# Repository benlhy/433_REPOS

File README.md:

# 433_REPOS
## Link to Homework 1
https://github.com/ndm736/ME433_2018/wiki/HW1

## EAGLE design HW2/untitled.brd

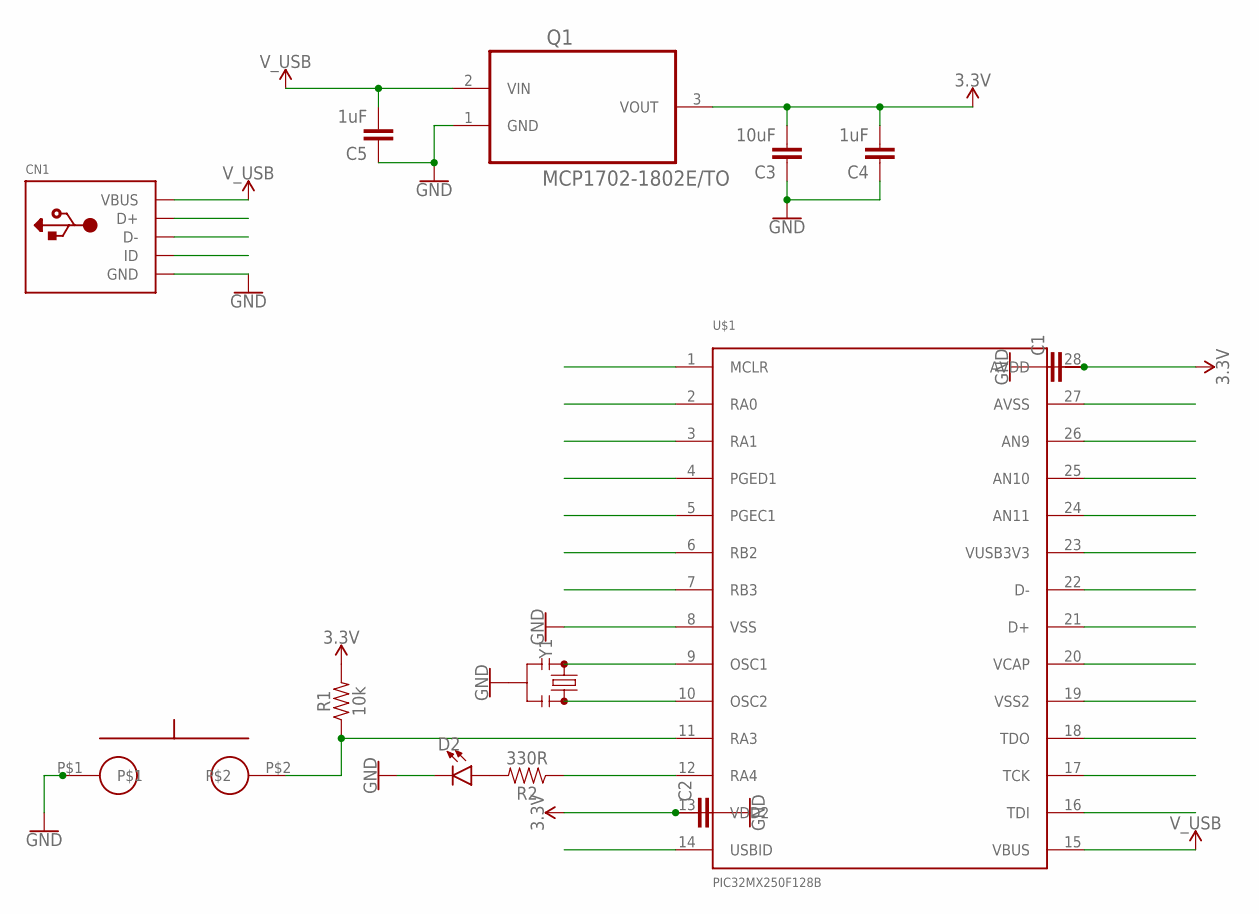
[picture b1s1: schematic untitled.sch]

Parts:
C1, C2: CAPVERT_CAP; PTH_VERT_CAP
C3: 10uF; PTH_VERT_CAP
C4, C5: 1uF; PTH_VERT_CAP
CN1: USBMINIB; USB-MINIB
D2: LED3MM; LED_3MM
Q1: MCP1702-1802E/TO; TO127P254X533-3
R1: 10k; AXIAL-0.3
R2: 330R; AXIAL-0.3
U$1: PIC32MX250F128B; DIP28
U$2: EVQ11
Y1: RESONATORPTH-7.6X3.8; RESONATOR-PTH-7.6X3.8

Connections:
3.3V: C1.P$2 (2), C2.P$1 (1), C3.P$2 (2), C4.P$2 (2), Q1.3 (VOUT), R1.P$2 (2), U$1.13 (VDD2), U$1.28 (AVDD)
D+: CN1.D+, U$1.21 (D+)
D-: CN1.D-, U$1.22 (D-)
GND: C1.P$1 (1), C2.P$2 (2), C3.P$1 (1), C4.P$1 (1), C5.P$1 (1), CN1.GND, D2.K (C), Q1.1 (GND), U$1.8 (VSS), U$2.P$1, Y1.2
ID: CN1.ID, U$1.14 (USBID)
MCLR: U$1.1 (MCLR)
unnamed: D2.A, R2.P$2 (2)
unnamed: U$1.9 (OSC1), Y1.1
unnamed: U$1.10 (OSC2), Y1.3
unnamed: R1.P$1 (1), U$1.11 (RA3), U$2.P$2
unnamed: R2.P$1 (1), U$1.12 (RA4)
PGC: U$1.5 (PGEC1)
PGD: U$1.4 (PGED1)
V_USB: C5.P$2 (2), CN1.VBUS, Q1.2 (VIN), U$1.15 (VBUS)

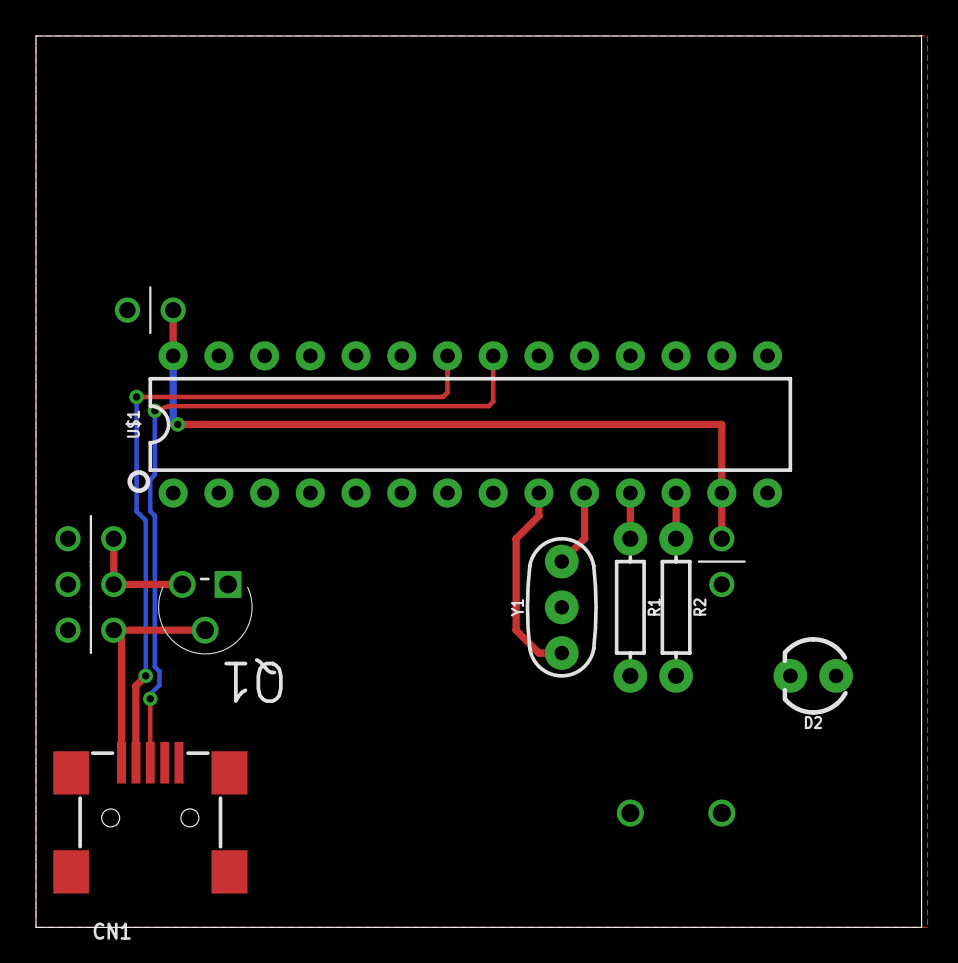
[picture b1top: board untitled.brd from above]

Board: 2 copper layers, 49.2 x 49.5 mm, 13 parts (0 on the bottom side), 11 nets.

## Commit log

2018-04-05 created proj
2018-04-05 LED working
2018-04-05 Blink LED at 1 sec
2018-04-05 Completed
2018-04-05 upload images
2018-04-06 Super duper schematics
2018-04-07 Update from another folder
2018-04-08 added circuit diagram
2018-04-12 Moved from HW2
2018-04-16 update code
2018-04-17 DAC works
2018-04-17 Update working code
2018-04-17 Modified code to change while loop
    was an if statement, changing it to a while loop fixed the issue of waiting 1ms.
2018-04-18 Made HW5, posted pictures
2018-04-20 update hw5
2018-04-20 cleared some old code from hw4
2018-04-20 added comments, changed speed to 53, changed I2C1 to I2C2
2018-04-20 cleared old code from main.c
2018-04-20 added writeExpander and readExpander functions
2018-04-20 updated initEpxander
2018-04-20 updated hw 5 and cleared hw 4 and hw 1
2018-04-20 update image
2018-04-24 made hw6 and imported
2018-04-24 removed unwanted code
2018-04-24 revert old file
2018-04-24 attempt to draw pixel on LED.
2018-04-24 all done
2018-04-26 create new project
2018-04-26 added i2c code from hw5
2018-04-26 changed
2018-04-26 i2c_init function
2018-04-27 updated code
2018-04-27 whoami works
2018-04-29 got i2c to work
2018-04-29 added LCD code
2018-04-29 updated hw7
2018-05-01 added hw8
2018-05-03 Lib init
2018-05-04 trying to fix errors
2018-05-04 Everything works
2018-05-10 built hw 10
2018-05-10 added iir
2018-05-10 fixed a bug
2018-05-11 hw11
2018-05-13 made new projects until one worked. Copying in and pasting code worked.
2018-05-13 update hw10 - fir wrong
2018-05-13 getting the math of fir ...
2018-05-13 math
2018-05-13 updated with correct code
2018-05-15 Created hard link to Android studio folder
2018-05-22 added hw14
2018-05-22 added cdc code to do this task
2018-05-22 added android
2018-05-28 Added pictures
2018-05-29 added images
2018-05-31 Created final project
2018-06-04 added final code and also moved HW13
2018-06-04 moved HW13
2018-06-10 Final firmware changes
2018-06-10 Android app
2018-06-10 small changes
2018-06-11 added photos!
2018-06-15 final update to fix exposure

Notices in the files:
parts and their libraries:
SparkFun-Resistors: Licensing: Creative Commons ShareAlike 4.0 International - https://creativecommons.org/licenses/by-sa/4.0
microbuilder: This work is placed in the public domain, and may be freely used for commercial and non-commercial work with the following conditions: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
